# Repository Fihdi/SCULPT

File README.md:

# 8hp ADSR Module

SCULPT is a 4 stage envelope generator with Attack, Decay, Sustain and Release control. Additionally, the Sustain level and the Release time can be voltage controlled. Engaging the LOOP switch connects the End-of-cycle (EOC) Gate back into the GATE input, turning the module into an LFO with variable rise and fall times.

While the module is in the sustain phase, an external CV source can be used to modulate the sustain level. The DECAY knob changes the slew rate of the SUS input during this stage.

A gate signal to the TRG input sets the module to the attack stage. 

By using a random voltage generator, the EOC output, together with the Release-CV input, can be used to create so-called "Krell patches".

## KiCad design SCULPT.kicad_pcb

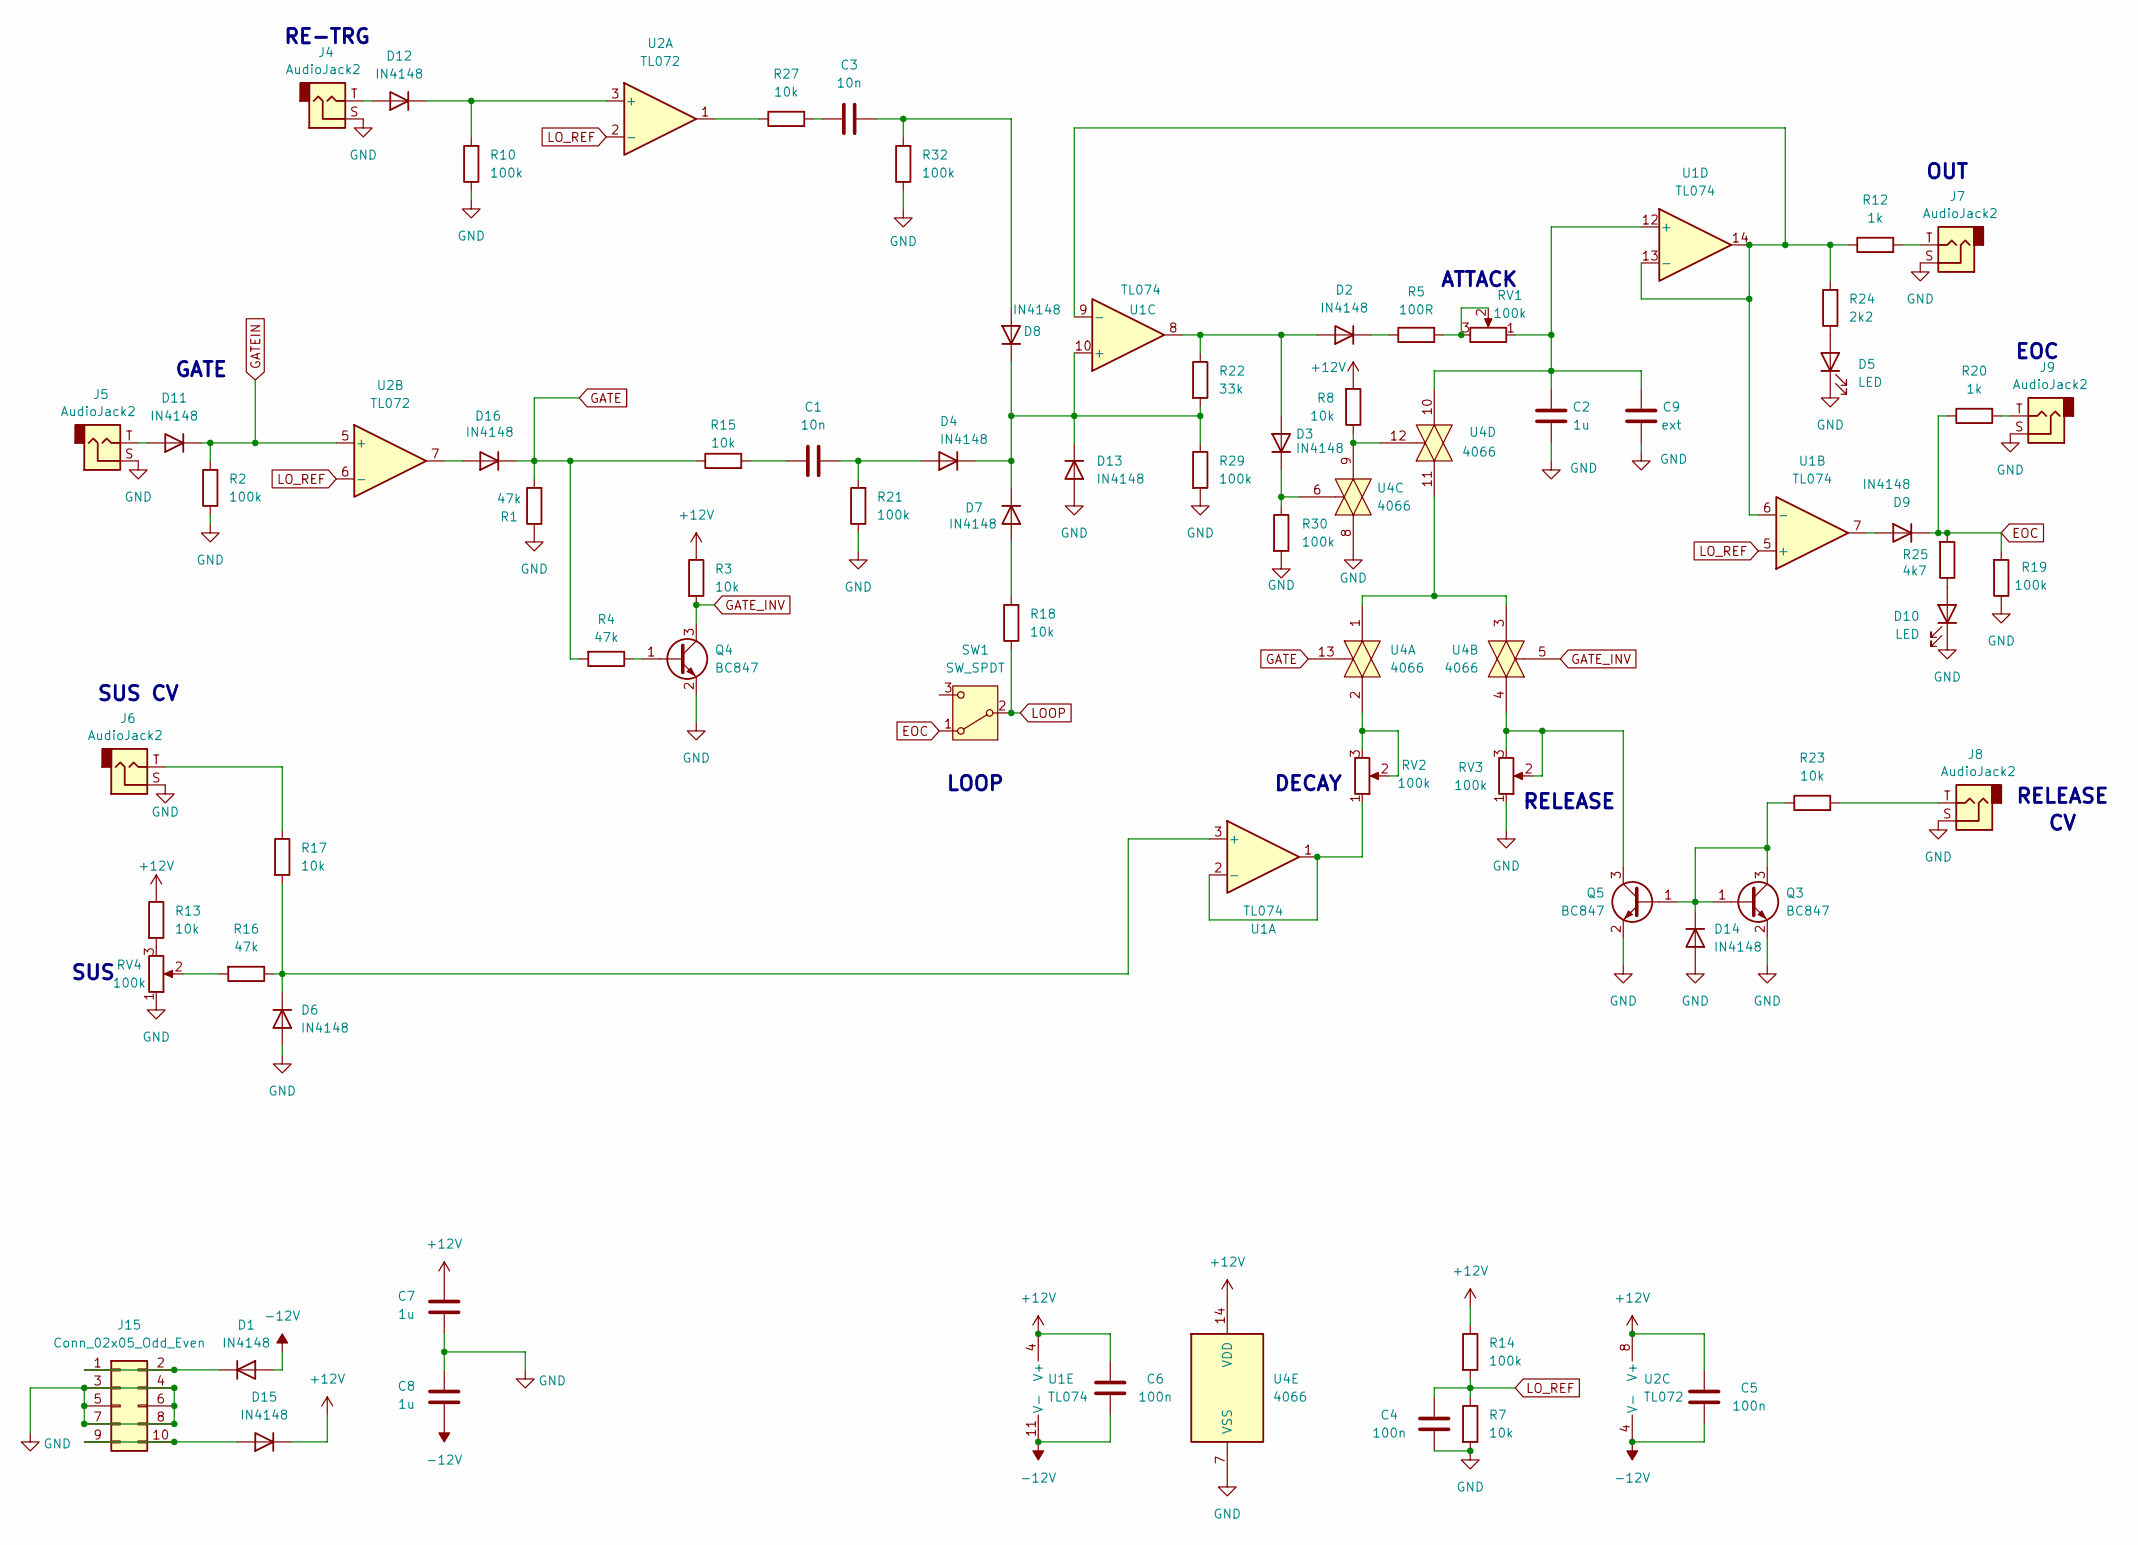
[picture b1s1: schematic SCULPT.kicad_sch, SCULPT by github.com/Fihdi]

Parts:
C1, C3: 10n; C_0805_2012Metric
C2, C7, C8: 1u; C_0805_2012Metric
C4, C5, C6: 100n; C_0805_2012Metric
C9: ext; C_Radial_D6.3mm_H11.0mm_P2.50mm
D1, D2, D3, D4, D6, D7, D8, D9, D11, D12, D13, D14, D15, D16: IN4148; D_SOD-323_HandSoldering
D5, D10: LED; LED_D3.0mm
J4, J5, J6, J7, J8, J9: AudioJack2; MonoTRS
J15: Conn_02x05_Odd_Even; IDC-Header_2x05_P2.54mm_Vertical
Q3, Q4, Q5: BC847; SOT-23
R1, R4, R16: 47k; R_0805_2012Metric
R2, R10, R14, R19, R21, R29, R30, R32: 100k; R_0805_2012Metric
R3, R7, R8, R13, R15, R17, R18, R23, R27: 10k; R_0805_2012Metric
R5: 100R; R_0805_2012Metric
R12, R20: 1k; R_0805_2012Metric
R22: 33k; R_0805_2012Metric
R24: 2k2; R_0805_2012Metric
R25: 4k7; R_0805_2012Metric
RV1, RV2, RV3, RV4: 100k; Potentiometer_Alpha_RD901F-40-00D_Single_Vertical
SW1: SW_SPDT; Switch
U1: TL074; SOIC-14_3.9x8.7mm_P1.27mm
U2: TL072; SOIC-8_3.9x4.9mm_P1.27mm
U4: 4066; SOIC-14_3.9x8.7mm_P1.27mm

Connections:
+12V: C5.1, C6.1, C7.1, D15.1 (K), R3.1, R8.2, R13.1, R14.1, U1.4 (V+), U2.8 (V+), U4.14 (VDD)
-12V: C5.2, C6.2, C8.2, D1.2 (A), U1.11 (V-), U2.4 (V-)
EOC: D9.1 (K), R19.2, R20.1, R25.2, SW1.1 (A)
GATE: D16.1 (K), R1.2, R4.2, R15.1, U4.13
GATEIN: D11.1 (K), R2.2, U2.5 (+)
GATE_INV: Q4.3 (C), R3.2, U4.5
GND: C2.1, C4.1, C7.2, C8.1, C9.1, D5.1 (K), D6.2 (A), D10.1 (K), D13.2 (A), D14.2 (A), J4.S, J5.S, J6.S, J7.S, J8.S, J9.S, J15.3, J15.4, J15.5, J15.6, J15.7, J15.8, Q3.2 (E), Q4.2 (E), Q5.2 (E), R1.1, R2.1, R7.2, R10.1, R19.1, R21.1, R29.2, R30.2, R32.1, RV3.1, RV4.1, U4.7 (VSS), U4.8
LOOP: R18.1, SW1.2 (B)
LO_REF: C4.2, R7.1, R14.2, U1.5 (+), U2.2 (-), U2.6 (-)
unnamed: C1.1, R15.2
unnamed: C3.1, R27.2
unnamed: D1.1 (K), J15.1, J15.2
unnamed: D2.2 (A), D3.2 (A), R22.1, U1.8
unnamed: D2.1 (K), R5.1
unnamed: D3.1 (K), R30.1, U4.6
unnamed: C1.2, D4.2 (A), R21.2
unnamed: D5.2 (A), R24.1
unnamed: D6.1 (K), R16.1, R17.2, U1.3 (+)
unnamed: D7.2 (A), R18.2
unnamed: C3.2, D8.2 (A), R32.2
unnamed: D9.2 (A), U1.7
unnamed: D10.2 (A), R25.1
unnamed: D11.2 (A), J5.T
unnamed: D12.2 (A), J4.T
unnamed: D12.1 (K), R10.2, U2.3 (+)
unnamed: D4.1 (K), D7.1 (K), D8.1 (K), D13.1 (K), R22.2, R29.1, U1.10 (+)
unnamed: D14.1 (K), Q3.1 (B), Q3.3 (C), Q5.1 (B), R23.1
unnamed: D15.2 (A), J15.9, J15.10
unnamed: D16.2 (A), U2.7
unnamed: J6.T, R17.1
unnamed: J7.T, R12.2
unnamed: J8.T, R23.2
unnamed: J9.T, R20.2
unnamed: Q4.1 (B), R4.1
unnamed: Q5.3 (C), RV3.2, RV3.3, U4.4
unnamed: R5.2, RV1.2, RV1.3
unnamed: R8.1, U4.9, U4.12
unnamed: R13.2, RV4.3
unnamed: R16.2, RV4.2
unnamed: R27.1, U2.1
unnamed: RV2.2, RV2.3, U4.2
unnamed: RV2.1, U1.1, U1.2 (-)
unnamed: R12.1, R24.2, U1.6 (-), U1.9 (-), U1.13 (-), U1.14
unnamed: C2.2, C9.2, RV1.1, U1.12 (+), U4.10
unnamed: U4.1, U4.3, U4.11

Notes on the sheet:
ATTACK
DECAY
LOOP
RELEASE
RE-TRG
SUS
GATE
SUS CV
EOC
OUT

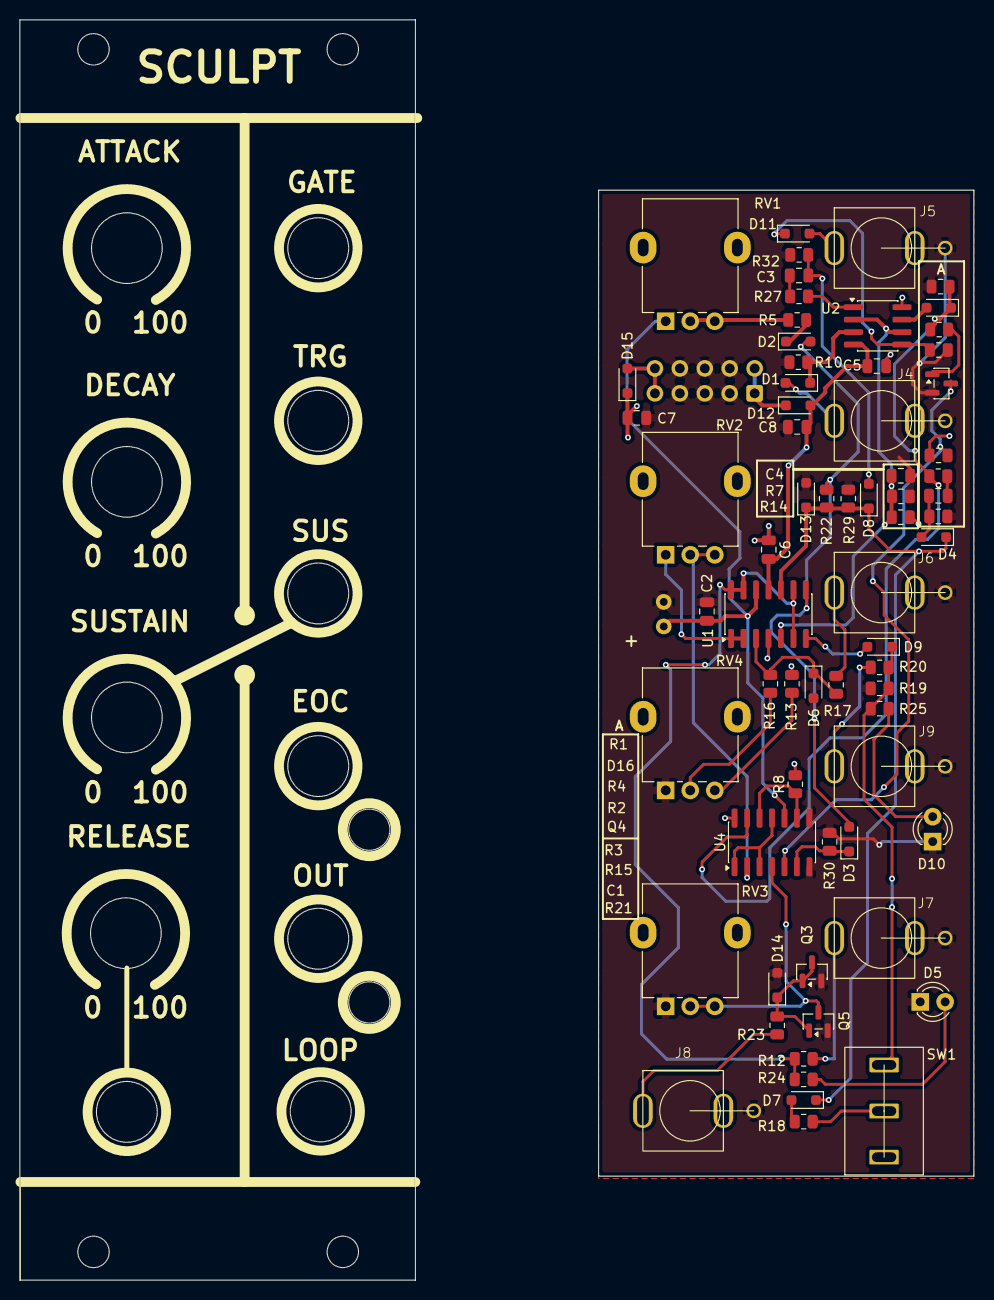
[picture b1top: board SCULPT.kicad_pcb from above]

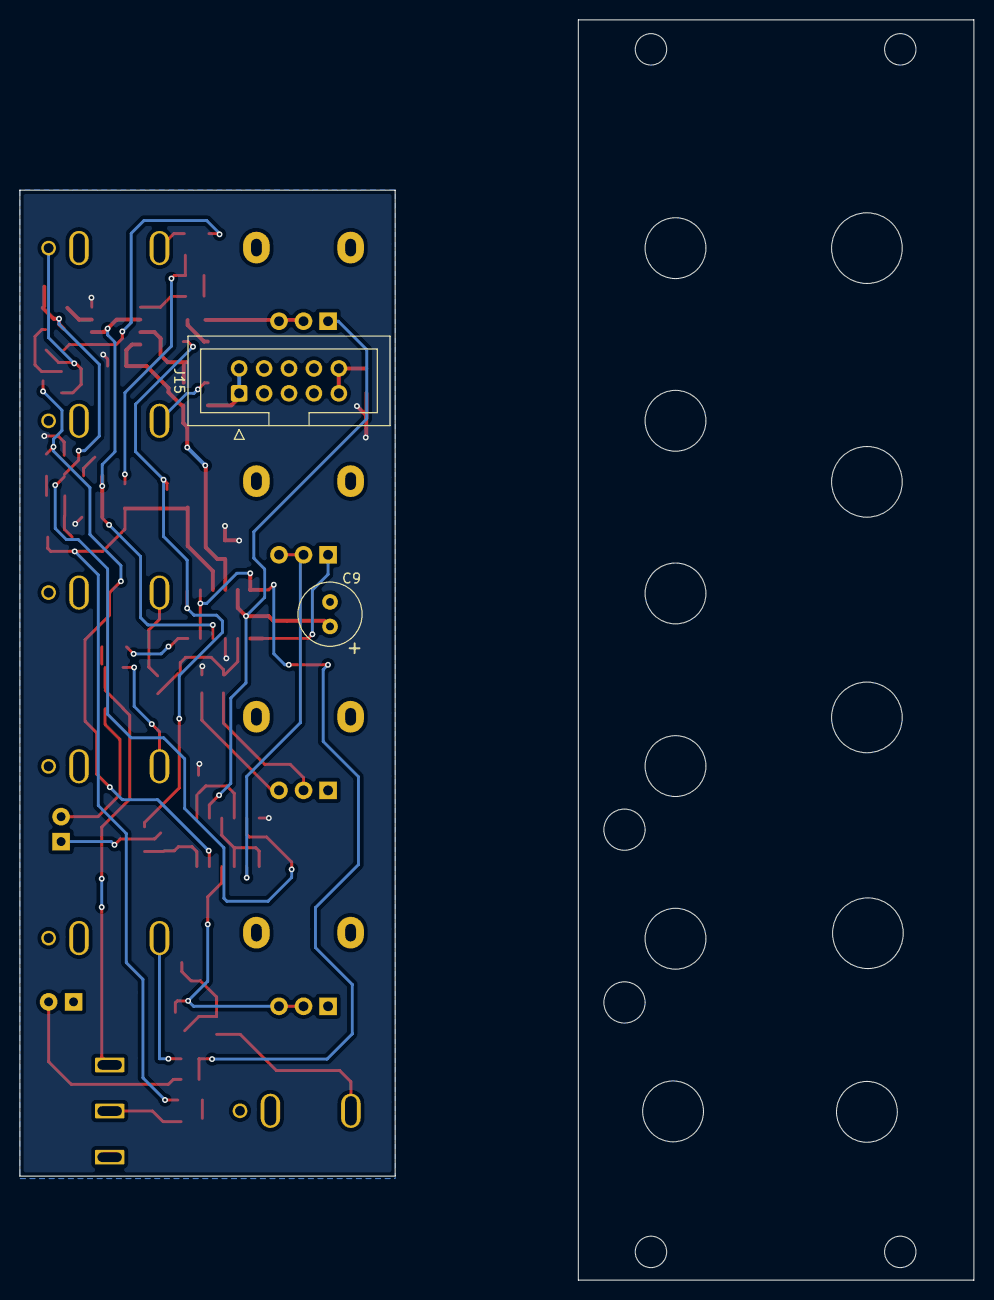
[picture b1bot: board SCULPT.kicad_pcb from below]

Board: 2 copper layers, 97.2 x 128.4 mm, 69 parts (2 on the bottom side), 45 nets.

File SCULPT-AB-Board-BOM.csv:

"Reference","Value","Footprint","Qty"
"C1,C3","10n","Capacitor_SMD:C_0805_2012Metric","2"
"C2,C7,C8","1u","Capacitor_SMD:C_0805_2012Metric","3"
"C4,C5,C6","100n","Capacitor_SMD:C_0805_2012Metric","3"
"C9","ext","Capacitor_THT:C_Radial_D6.3mm_H11.0mm_P2.50mm","1"
"D1,D2,D3,D4,D6,D7,D8,D9,D11,D12,D13,D14,D15,D16","IN4148","Diode_SMD:D_SOD-323_HandSoldering","14"
"D5,D10","LED","LED_THT:LED_D3.0mm","2"
"J4,J5,J6,J7,J8,J9","AudioJack2","Library:MonoTRS","6"
"J15","Conn_02x05_Odd_Even","Connector_IDC:IDC-Header_2x05_P2.54mm_Vertical","1"
"Q3,Q4,Q5","BC847","Package_TO_SOT_SMD:SOT-23","3"
"R1,R4,R16","47k","Resistor_SMD:R_0805_2012Metric","3"
"R2,R10,R14,R19,R21,R29,R30,R32","100k","Resistor_SMD:R_0805_2012Metric","8"
"R3,R7,R8,R13,R15,R17,R18,R23,R27","10k","Resistor_SMD:R_0805_2012Metric","9"
"R5","100R","Resistor_SMD:R_0805_2012Metric","1"
"R12,R20","1k","Resistor_SMD:R_0805_2012Metric","2"
"R22","33k","Resistor_SMD:R_0805_2012Metric","1"
"R24","2k2","Resistor_SMD:R_0805_2012Metric","1"
"R25","4k7","Resistor_SMD:R_0805_2012Metric","1"
"RV1,RV2,RV3,RV4","100k","Potentiometer_THT:Potentiometer_Alpha_RD901F-40-00D_Single_Vertical","4"
"SW1","SW_SPDT","Library:Switch","1"
"U1","TL074","Package_SO:SOIC-14_3.9x8.7mm_P1.27mm","1"
"U2","TL072","Package_SO:SOIC-8_3.9x4.9mm_P1.27mm","1"
"U4","4066","Package_SO:SOIC-14_3.9x8.7mm_P1.27mm","1"
